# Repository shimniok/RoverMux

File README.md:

RoverMux is an Remote Control multiplexer for use with Autonomous Ground Vehicles (Rovers). With it installed, you can
quickly and easily switch between remote control and autonomous control of your autonomous rover.

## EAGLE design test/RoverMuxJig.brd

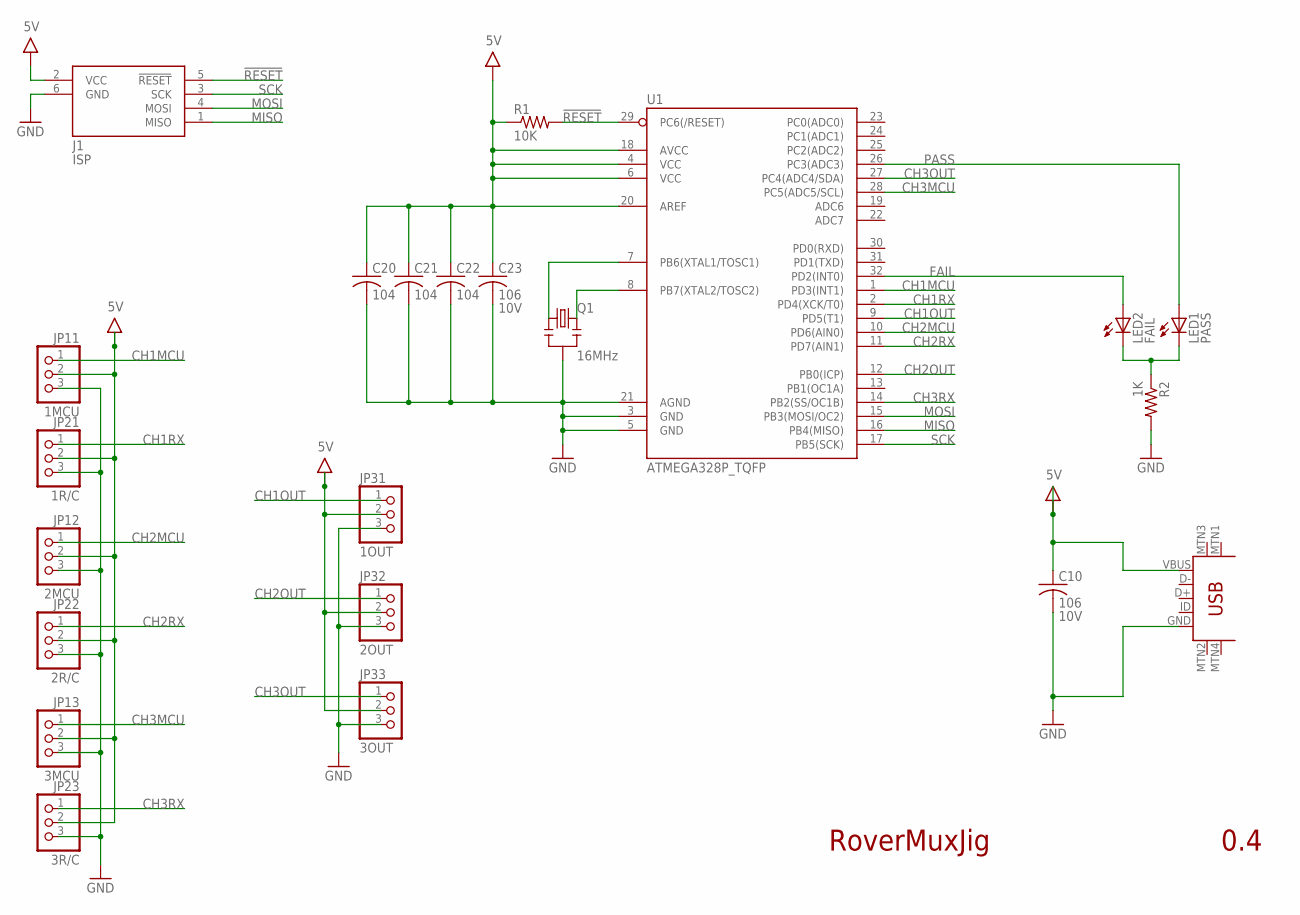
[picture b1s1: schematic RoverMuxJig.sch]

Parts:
C10, C23: 106; C0603; VOLTAGE 10V; PARTNO CL10A106MP8NNNC
C20, C21, C22: 104; C0603; PARTNO C1608X7R1E104K080AA
J1: ISP; CON6P2R
JP11: 1MCU; 1X03-S
JP12: 2MCU; 1X03-S
JP13: 3MCU; 1X03-S
JP21: 1R/C; 1X03-S
JP22: 2R/C; 1X03-S
JP23: 3R/C; 1X03-S
JP31: 1OUT; 1X03-S
JP32: 2OUT; 1X03-S
JP33: 3OUT; 1X03-S
LED1: PASS; CHIPLED_1206; PARTNO LH N974-KN-1
LED2: FAIL; CHIPLED_1206; PARTNO LG N971-KN-1
Q1: 16MHz; CSTCE_V_C
R1: 10K; R0603; PARTNO RC0603JR-07330RL
R2: 1K; R0603; PARTNO RC0603JR-07330RL
U1: ATMEGA328P_TQFP; TQFP32-08
U$4: USB-MINIB-5PIN; USB-MINIB

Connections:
5V: C10.1, C20.1, C21.1, C22.1, C23.1, J1.2 (VCC), JP11.2, JP12.2, JP13.2, JP21.2, JP22.2, JP23.2, JP31.2, JP32.2, JP33.2, R1.1, U1.4 (VCC), U1.6 (VCC), U1.18 (AVCC), U1.20 (AREF), U$4.VBUS; also elsewhere on the board
!RESET: J1.5 (!RESET), R1.2, U1.29 (PC6(/RESET)); also elsewhere on the board
CH1MCU: JP11.1, U1.1 (PD3(INT1))
CH1OUT: JP31.1, U1.9 (PD5(T1))
CH1RX: JP21.1, U1.2 (PD4(XCK/T0))
CH2MCU: JP12.1, U1.10 (PD6(AIN0))
CH2OUT: JP32.1, U1.12 (PB0(ICP))
CH2RX: JP22.1, U1.11 (PD7(AIN1))
CH3MCU: JP13.1, U1.28 (PC5(ADC5/SCL))
CH3OUT: JP33.1, U1.27 (PC4(ADC4/SDA))
CH3RX: JP23.1, U1.14 (PB2(SS/OC1B))
FAIL: LED2.A, U1.32 (PD2(INT0))
GND: C10.2, C20.2, C21.2, C22.2, C23.2, J1.6 (GND), JP11.3, JP12.3, JP13.3, JP21.3, JP22.3, JP23.3, JP31.3, JP32.3, JP33.3, Q1.GND, R2.2, U1.3 (GND), U1.5 (GND), U1.21 (AGND), U$4.GND; also elsewhere on the board
MISO: J1.1 (MISO), U1.16 (PB4(MISO))
MOSI: J1.4 (MOSI), U1.15 (PB3(MOSI/OC2))
unnamed: Q1.X2, U1.8 (PB7(XTAL2/TOSC2))
unnamed: Q1.X1, U1.7 (PB6(XTAL1/TOSC1))
unnamed: LED1.C, LED2.C, R2.1
PASS: LED1.A, U1.26 (PC3(ADC3))
RX<: U1.30 (PD0(RXD)); also elsewhere on the board
SCK: J1.3 (SCK), U1.17 (PB5(SCK))
TX>: U1.31 (PD1(TXD)); also elsewhere on the board

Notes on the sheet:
RoverMuxJig
0.4

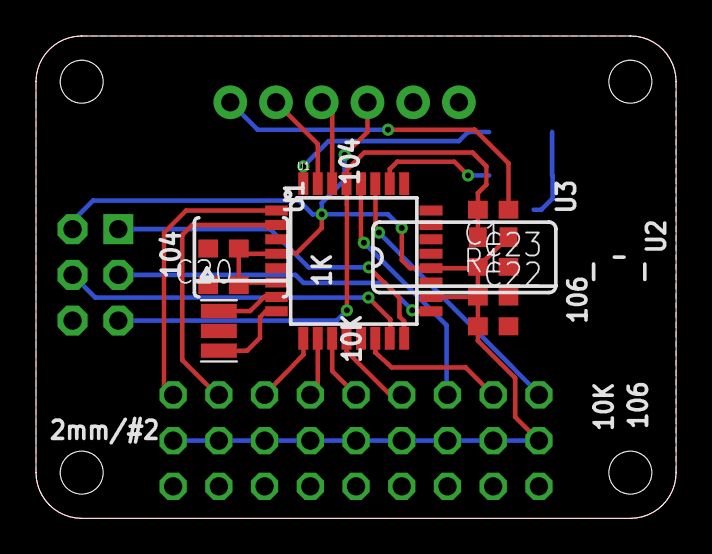
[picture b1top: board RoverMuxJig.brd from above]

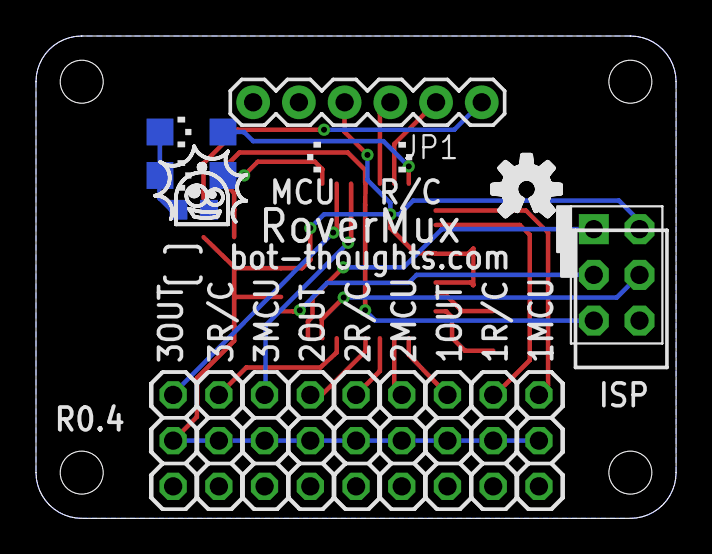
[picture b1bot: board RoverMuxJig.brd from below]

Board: 2 copper layers, 35.6 x 26.8 mm, 23 parts (14 on the bottom side), 23 nets.

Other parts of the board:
C1: 104; C0603
JP1: FTDI; FTDI_BASIC

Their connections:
5V: JP1.VCC; also elsewhere on the board
!RESET: C1.2; also elsewhere on the board
GND: JP1.GND; also elsewhere on the board
unnamed: C1.1, JP1.DTR
RX<: JP1.TXO; also elsewhere on the board
TX>: JP1.RXI; also elsewhere on the board

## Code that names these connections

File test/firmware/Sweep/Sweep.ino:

#include <TimerOne.h>
#include <Servo.h> 

// Servo IDs
#define RC1   0
#define MCU1  1
#define RC2   2
#define MCU2  3
#define RC3   4
#define MCU3  5

// Pins
#define CH1OUT  8
#define CH1RC   9
#define CH1MCU 10
#define CH2OUT  5
#define CH2RC   6
#define CH2MCU  7
#define CH3OUT  2
#define CH3RC   3
#define CH3MCU  4

#define MCU1DUR 10
#define MCU2DUR 11
#define MCU3DUR 12
#define RC1DUR  14
#define RC2DUR  15
#define RC3DURL 13
#define RC3DURH 17

#define PAUSE 2000

// Channel check errors
#define CON_NONE  0x00             // Both outputs are low
#define CON_MCU   0x01             // MCU connected
#define CON_RC    0x02             // RC connected
#define CON_BOTH  (CON_MCU|CON_RC) // Both outputs are high
#define CON_ERR   0x04             // Flags a connection error of some kind

Servo ch1;
Servo ch3;
 
void setup() 
{  
  Timer1.initialize(100);  // 100usec
  Timer1.attachInterrupt(servoHandler);
  Timer1.start();

  servoPin(RC1, CH1RC); 
  servoPin(MCU1, CH1MCU);
  servoPin(RC2, CH2RC);
  servoPin(MCU2, CH2MCU);
  servoPin(RC3, CH3RC);
  servoPin(MCU3, CH3MCU); 

  servoInPin(CH1OUT);
  servoInPin(CH2OUT);
  servoInPin(CH3OUT);
 
  servoSet(MCU1, MCU1DUR);
  servoSet(MCU2, MCU2DUR);
  servoSet(MCU3, MCU3DUR);
    
  Serial.begin(9600);
} 


void displayServos()
{
  Serial.print(" CH1OUT: ");
  Serial.print(getDuration(CH1OUT));
  Serial.print(" CH2OUT: ");
  Serial.print(getDuration(CH2OUT));
  Serial.print(" CH3OUT: ");
  Serial.print(getDuration(CH3OUT));
  Serial.println();
}

boolean checkChannel(long dur, long desired)
{
  boolean result;
  
  if (dur == result) {
    Serial.print("OK ");
  } else {
    Serial.print("BAD ");
  }
  
  return result;
}
 
void loop() 
{ 
  servoSet(RC1, 0);
  servoSet(RC2, 0);
  servoSet(RC3, 0);
  delay(PAUSE);
  displayServos();

  servoSet(RC1, RC1DUR);
  servoSet(RC2, RC2DUR);
  servoSet(RC3, 0);
  delay(PAUSE);
  displayServos();

  servoSet(RC1, RC1DUR);
  servoSet(RC2, RC2DUR);
  servoSet(RC3, RC3DURL);
  delay(PAUSE);
  displayServos();

  servoSet(RC1, RC1DUR);
  servoSet(RC2, RC2DUR);
  servoSet(RC3, RC3DURH);
  delay(PAUSE);
  displayServos();

  Serial.println("----------------------------------");
} 

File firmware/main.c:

/*
 * main.c
 *
 * This firmware runs an RC multiplexer that switches between autonomous and manual control of a robot.
 * A timeout value is subtracted every ~10us. If an RC signal is present, this timeout is reset and Manual
 * Mode is selected. When no RC signal is present for the duration of the timeout period, Autonomous Mode
 * is selected.
 *
 *  Created on: Jul 12, 2013
 *      Author: mes
 */

#include <avr/io.h>
#include <avr/interrupt.h>
#include <util/delay.h>

/*************** DEFINITIONS ****************/

#define CH1RX       PB2
#define CH1INT      PCINT2
#define CH3RX       PB0
#define CH3INT      PCINT0

#define MINPERIOD   5000L
#define MAXPERIOD   50000L
#define MINONTIME   300L
#define MAXONTIME   3000L

#define MCUenable   PB4
#define RCenable    PB3

#define VALIDCNT    3			// number of valid signals required to go manual
#define DT          100			// delta time for ticks, usec
#define TIMEOUT     60000L			// timeout in microseconds

/************* GLOBAL VARIABLES **************/

// CH1
uint8_t inactive1=VALIDCNT;			// RX signal active pulse counter,
long ontime1;  					// measure length of signal on time
long offtime1; 					// measure length of signal off time
uint8_t history1;				// history of pin states

// CH3
uint8_t inactive3=VALIDCNT;			// RX signal active pulse counter
long ontime3;  					// measure length of signal on time
long offtime3; 					// measure length of signal off time
uint8_t history3;				// history of pin states

/****************** CODE *********************/

int main() {
	// setup pins for output
	// This is in the main routine instead of a function to save a few bytes of flash
	DDRB = (1<<MCUenable)|(1<<RCenable);

	// Setup timer to keep track of timing of signal
	// This is in the main routine instead of a function to save a few bytes of flash
	//
	TCCR0A = (1<<WGM01);			// CTC mode
	TCCR0B = (0<<CS02)|(1<<CS01)|(0<<CS00); // clk/8, 9.6MHz -> 1.2MHz
	OCR0A = 111; 				// 1.2MHz / 120 -> 10kHz, 100usec
	TIMSK0 = (1<<OCIE0A);			// Enable output compare A interrupt

	/* Ready to receive interrupts, now */
	sei();

	while (1);
}


/**
 * Timer interrupt handler, fires periodically, counts on time, off time, and manages signal timeout
 */
ISR(TIM0_COMPA_vect) {

	// Count on time and off time for CH1
	history1 <<= 1;
	if ((PINB & (1<<CH1RX)) == 0) {
		offtime1 += DT;  // track off time
		// Does the signal off time exceeds the timeout?
		if (offtime1 > TIMEOUT) {
			inactive1 = VALIDCNT;
		}
	} else {
		ontime1 += DT;   // track on time
		history1 |= 1;
	}

	long p;
	// Positive edge
	if (history1 == 0b00000001) {
		p = ontime1+offtime1;
		if (inactive1 && p > MINPERIOD && p < MAXPERIOD && ontime1 > MINONTIME && ontime1 < MAXONTIME) {
			// Enable RC if CH1 active but CH3 inactive
			if ((--inactive1 == 0) && inactive3) {
				PORTB = (1<<RCenable);
			}
		}
		ontime1 = 0;
	}
	// Negative edge
	if (history1 == 0b11111110) {
		offtime1 = 0;
	}

	// Count on time and off time for CH3
	history3 <<= 1;
	if ((PINB & (1<<CH3RX)) == 0) {
		offtime3 += DT;  // track off time
		// Does the signal off time exceeds the timeout?
		if (offtime3 > TIMEOUT) {
			inactive3 = VALIDCNT;
		}
	} else {
		ontime3 += DT;   // track on time
		history3 |= 1;
	}

	// Positive edge
	if (history3 == 0b00000001) {
		p = ontime3+offtime3;
		if (inactive3 && p > MINPERIOD && p < MAXPERIOD && ontime3 > MINONTIME && ontime3 < MAXONTIME) {
			--inactive3; // using a single variable to conserve program memory
		}
		// Enable RC if CH3 active and CH3 on time > 1.5ms, else disable RC
		if (!inactive3) {
			if (ontime3 > 1500) {
				PORTB = (1<<RCenable);
			} else {
				PORTB = (1<<MCUenable);
			}
		}
		ontime3 = offtime3 = 0;
	}
	// Negative edge
	if (history3 == 0b11111110) {
		offtime3 = 0;
	}

	// If both CH1 and CH3 have timed out, disable RC
	if (inactive1 && inactive3) {
		PORTB = (1<<MCUenable);
	}
}

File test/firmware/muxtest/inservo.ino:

uint16_t tstart[20]; // start time
uint16_t tdur[20];   // duration
byte prevb, prevc, prevd; // previous pin states


void servoTimer(byte pin) {
  *digitalPinToPCMSK(pin) |= bit (digitalPinToPCMSKbit(pin));  // enable pin
  PCIFR  |= bit (digitalPinToPCICRbit(pin)); // clear any outstanding interrupt
  PCICR  |= bit (digitalPinToPCICRbit(pin)); // enable interrupt for the group
  tstart[pin] = 0;
  tdur[pin] = 0;
  prevb = PINB;
  prevc = PINC;
  prevd = PIND;
}


void resetDurations() {
  for (int i=0; i < 20; i++) {
    tstart[i] = 0;
    tdur[i] = 0;
  }
}


uint16_t getDuration(byte pin) {
  uint16_t dur;
 
  dur = (pin >= 0 && pin < 20) ? tdur[pin] : 0;

  return dur;
}


// handle pin change interrupt for D8 to D13 here
ISR (PCINT0_vect) {
  byte changed;
  const byte offset = 8; // PB0 ==> D8
  
  changed = PINB ^ prevb;
  prevb = PINB;
  
  for (int i = 0; i <= 5; i++) { // PB0..PB5

    byte b = (1<<i);
    if (b & changed) {
      
      if (PINB & b) { // high
        tstart[i+offset] = micros();
      } else {        // low
        tdur[i+offset] = micros() - tstart[i+offset];
      }

    } // if changed

  } // for 
 
} // PCINT0_vect
 

// handle pin change interrupt for A0 to A5 here 
ISR (PCINT1_vect) {
  byte changed; 
  const byte offset = 14; // PC0 ==> D14
} // PCINT1_vect


// handle pin change interrupt for D0 to D7 here
ISR (PCINT2_vect) {
  const byte offset = 0; // PD0 ==> D0
  byte changed;

  changed = PIND ^ prevd;
  prevd = PIND;
  
  for (int i = 0; i <= 7; i++) { // PD0..PD7

    byte b = (1<<i);
    if (b & changed) {

      if (PIND & b) { // high
        tstart[i+offset] = micros();
      } else {        // low
        tdur[i+offset] = micros() - tstart[i+offset];
      }

    } // if changed

  } // for

} // PCINT2_vect
 

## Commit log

2013-10-01 Consolidated RoverMux electronics and software directories under a single top-level directory
2013-10-01 Added eclipse settings and files
2013-10-01 Adding eclipse makefiles
2013-10-02 Created RoverMeter for measuring V/A
2013-10-02 Updated to fix LED indicator circuits, add AVRISP, moved LEDs, rerouted traces.
2013-10-02 Renamed to RoverMux
2013-10-02 Revised for AVRISP female fitment
2013-10-10 Revised schematic changing LED indicator circuit to fix design flaw.
2013-11-04 RoverMux electronics changes, minor software changes
2014-01-29 Revised 8SOIC footprint, replaced 5V regulator and selector with 3.3V regulator to simplify. Moved devices around, simplified routing to pin headers. Placed missing ISP trace. Revised schematic layou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
2014-01-29 Added silkscreen, version 0.4 as ordered.
2015-05-07 Added README and LICENSE
2015-08-09 Added standalone makefile
2015-08-09 Removed Release AVRStudio directory
2015-08-09 renamed software to firmware
2015-08-12 Added User Guide
2015-08-12 updated userguide for better image quality
2015-10-06 Added test jig
2015-10-08 basic servo signals and data structures
2015-10-08 Added on/off capability, 6 channels, functions for on/off and setting period
2015-10-08 Revised variable names, consolidated servoon/off into servoSet.
2015-10-08 Attempt to manually control servo outputs and inputs
2015-10-08 Updated jig
2015-10-08 removed efuse from makefile
2015-10-08 Created new test firmware
2015-10-08 removed non-working test firmware
2015-10-08 moved eagle files to subdir
2015-10-08 added *.silk to gitignore
2015-10-09 Initial attempt to set up servo signal pin timing
2015-10-09 Implemented timer check for CH1OUT, one test case
2015-10-09 monitoring multiple tests, multiple channels. possible bug with ch3 monitoring?
2015-10-09 fixed issues with counter resets resulting in incorrect duration counts
2020-01-08 tabs to spaces
2020-01-08 Updated programmers

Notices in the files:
parts and their libraries:
SparkFun-Connectors: Licensing: Creative Commons ShareAlike 4.0 International - https://creativecommons.org/licenses/by-sa/4.0
